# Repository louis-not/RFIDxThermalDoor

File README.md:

# RFIDxThermalDoor
[Indonesia]
Alat Pengunci Pintu Contactless berbasis RFID dan Sensor Suhu Infrared didesain dengan mempertimbangkan kondisi pandemi yang bertujuan untuk mengurangi kontak gagang pintu dengan tangan pengguna. Alat ini dapat digunakan dengan mengintegrasikan dengan sistem pengunci pintu konvensional atau sebagai mekanisme penguncian pintu atau digunakan sebagai stand-alone device.

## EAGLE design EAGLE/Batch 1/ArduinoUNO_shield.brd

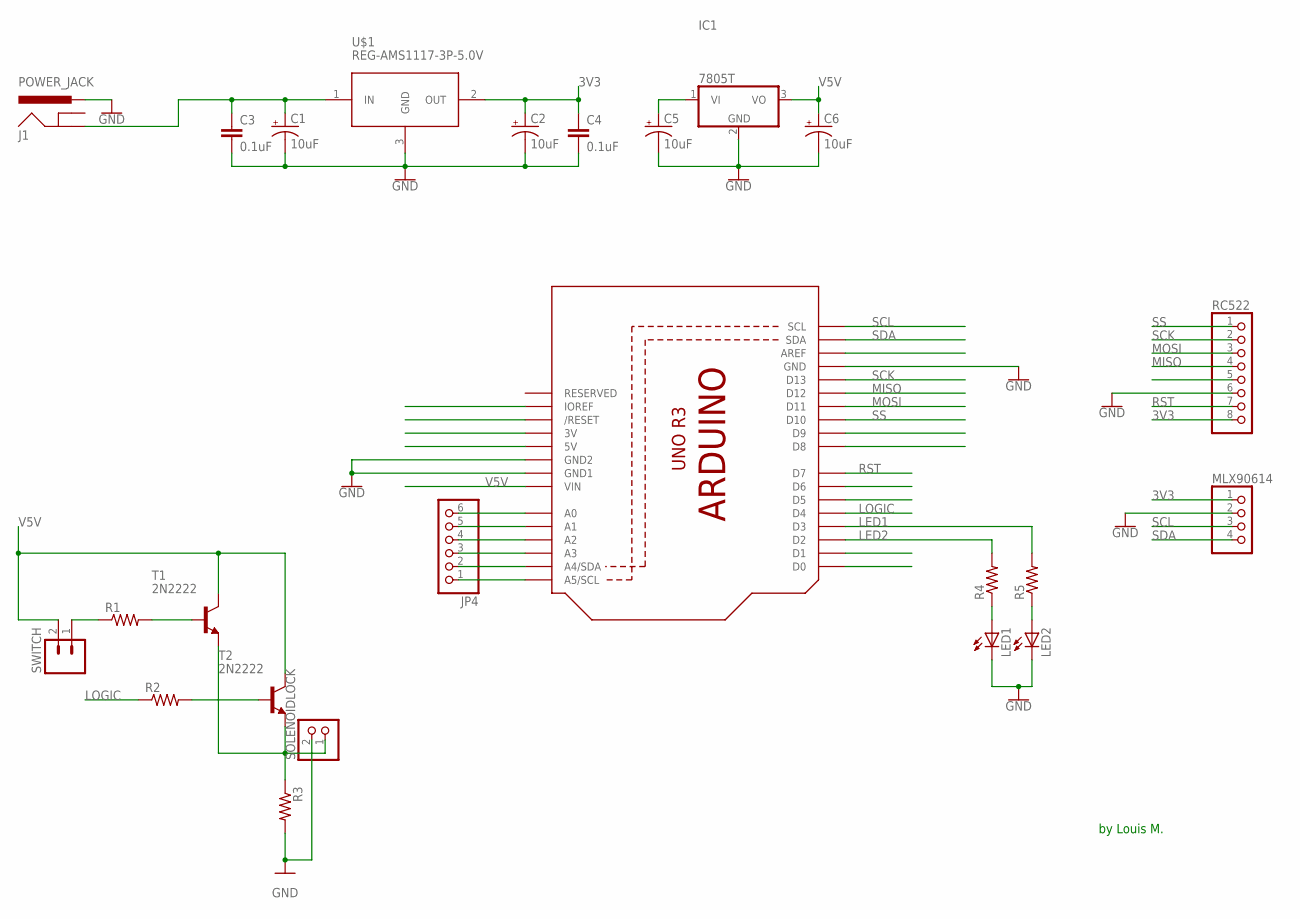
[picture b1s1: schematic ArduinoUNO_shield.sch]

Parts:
C1, C2: 10uF; CPOL-RADIAL-2.5MM-5MM-KIT
C3, C4: 0.1uF; CAP-PTH-SMALL-KIT
C5, C6: 10uF; CPOL-RADIAL-2.5MM-5MM
IC1: 7805T; TO220H
J1: POWER_JACK; POWER_JACK_PTH
JP4: PINHD-1X6B; 1X06-BIG
LED1, LED2: LED5MM
MLX90614: PINHD-1X4; 1X04
R1, R2, R3: R-US_0207/10; 0207/10
R4, R5: R-US_0204/5; 0204/5
RC522: PINHD-1X8; 1X08
SOLENOIDLOCK: JST_2PIN-THM-RA; JST-PH-2-THM-RA
SWITCH: M02; 02P
T1, T2: 2N2222; TO92-EBC-OVAL
U$1: REG-AMS1117-3P-5.0V; REG-AMS1117-3P
UNOR3: ARDUINOR3-DIMENSION; ARDUINOR3

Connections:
3V3: C2.1 (+), C4.1, MLX90614.1, RC522.8, U$1.2 (OUT)
GND: C1.2 (-), C2.2 (-), C3.2, C4.2, C5.2 (-), C6.2 (-), IC1.2 (GND), J1.PWR, LED1.K (C), LED2.K (C), MLX90614.2, R3.2, RC522.6, SOLENOIDLOCK.2 (1), U$1.3 (GND), UNOR3.GND, UNOR3.GND1, UNOR3.GND2
LED1: R5.2, UNOR3.D3
LED2: R4.2, UNOR3.D2
LOGIC: R2.1, UNOR3.D4
MISO: RC522.4, UNOR3.D12
MOSI: RC522.3, UNOR3.D11
unnamed: R1.2, T1.B
unnamed: R1.1, SWITCH.1
unnamed: R2.2, T2.B
unnamed: LED1.A, R4.1
unnamed: R3.1, SOLENOIDLOCK.1 (2), T1.E, T2.E
unnamed: LED2.A, R5.1
unnamed: C5.1 (+), IC1.1 (VI)
unnamed: C1.1 (+), C3.1, J1.GND, U$1.1 (IN)
unnamed: JP4.6, UNOR3.A0
unnamed: JP4.5, UNOR3.A1
unnamed: JP4.4, UNOR3.A2
unnamed: JP4.3, UNOR3.A3
unnamed: JP4.2, UNOR3.A4 (A4/SDA)
unnamed: JP4.1, UNOR3.A5 (A5/SCL)
RST: RC522.7, UNOR3.D7
SCK: RC522.2, UNOR3.D13
SCL: MLX90614.3, UNOR3.SCL
SDA: MLX90614.4, UNOR3.SDA
SS: RC522.1, UNOR3.D10
V5V: C6.1 (+), IC1.3 (VO), SWITCH.2, T1.C, T2.C, UNOR3.VIN

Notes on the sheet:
by Louis M.

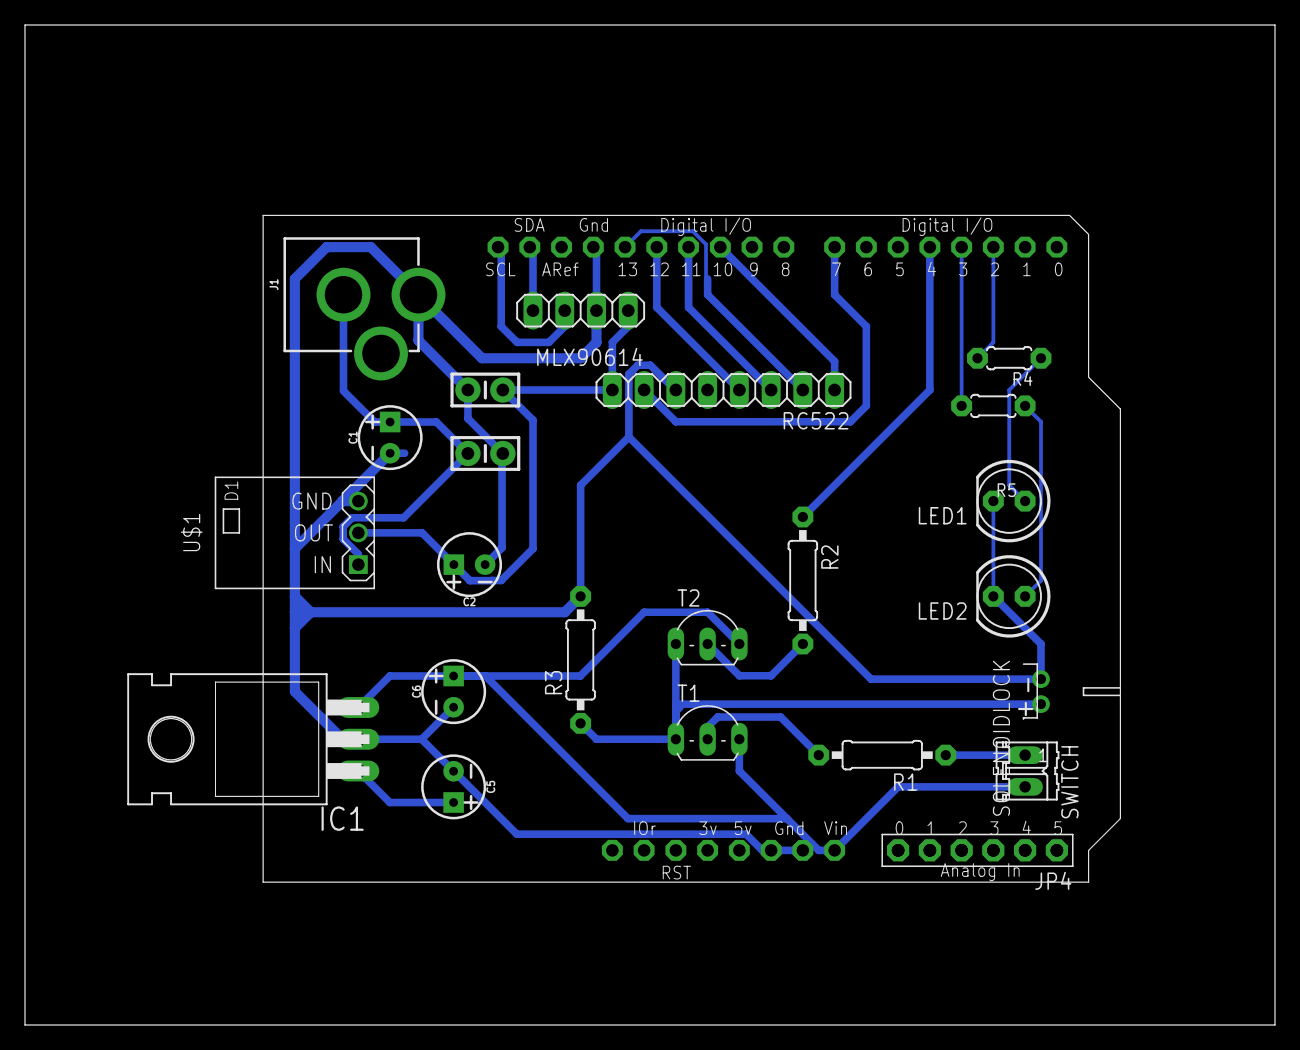
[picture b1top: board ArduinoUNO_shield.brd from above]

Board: 2 copper layers, 100.0 x 80.0 mm, 24 parts (0 on the bottom side), 27 nets.

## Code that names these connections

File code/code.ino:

#include <SPI.h>  // RFID
#include <MFRC522.h> // RFID Sensor
#include <Wire.h> // I2C, for Thermometre
#include <avr/wdt.h> // Watchdog timer
#include <Adafruit_MLX90614.h> // thermometer
#define SS_PIN 10 // RFID
#define RST_PIN 7 // RFID
#define LOGIC 4
#define LED1 2 // Red
#define LED2 3 // Blue


MFRC522 mfrc522(SS_PIN, RST_PIN); 
Adafruit_MLX90614 mlx = Adafruit_MLX90614();

void setup() {
  Serial.begin(57600) ;
  SPI.begin();
  
  // RFID Setup
  mfrc522.PCD_Init() ;
  Serial.println("Setup 1");

  // RELAY Setup
  pinMode(LOGIC, OUTPUT) ;
  Serial.println("Setup 2");
  
  // Temperature Setup
  const int constant = 1.5 ;// kalibrasi thermometer terhadap jarak pengukuran 5 cm
  mlx.begin();
  Serial.println("Setup 3");
  
  // Indicator Setup
  pinMode(LED1, OUTPUT) ;
  pinMode(LED2, OUTPUT) ;
  Serial.println("Setup 4");
  
  // Watchdog timer setup 
//  wdt_enable(WDTO_8S) ;
  Serial.println("Setup 5");
  
  // Success Setup
  for (int i = 0; i < 3 ; i++ ){
    digitalWrite(LED1, HIGH);
    delay(500) ;
    digitalWrite(LED1, LOW) ;  
  }
  Serial.println("Setup Success");
}

void loop() {
  wdt_reset() ;
//  Serial.println("Begin test") ;
  if ( ! mfrc522.PICC_IsNewCardPresent()) 
  {
    return;
  }
  // Select one of the cards
  if ( ! mfrc522.PICC_ReadCardSerial()) 
  {
    return;
  }
  Serial.println("pass") ;
  String userID = "";
  byte letter ;
  for (byte i = 0; i < mfrc522.uid.size; i++){
     Serial.print(mfrc522.uid.uidByte[i] < 0x10 ? " 0" : " ");
     Serial.print(mfrc522.uid.uidByte[i], HEX);
     userID.concat(String(mfrc522.uid.uidByte[i] < 0x10 ? " 0" : " "));
     userID.concat(String(mfrc522.uid.uidByte[i], HEX));
  }
  wdt_reset() ;
  Serial.println();
  userID.toUpperCase();
  if (userID.substring(1) == "02 AC 7E D1 E1 0E B0" || userID.substring(1) == "E5 AD 8D 4F") {
    digitalWrite(LED1, HIGH) ;
    Tempcheck() ;   
    delay(2000) ;
  } else {
    delay(2000) ;
  }

  //reset indicator
  digitalWrite(LED1, LOW);
  digitalWrite(LED2, LOW);
  Serial.println("reset complete") ;
  delay(2000);
}

void Tempcheck(){
  wdt_reset() ;
  while (1){
    float temp = mlx.readObjectTempC() ;
    if (temp > 34 && temp < 40) {
      Serial.println(temp) ;
      if (temp >= 37 ){
        digitalWrite(LED1, LOW) ;
        Serial.println("GO AWAY");
        } else {
        Serial.println("GET IN!") ;
        digitalWrite(LED2, HIGH) ;
        digitalWrite(LOGIC, HIGH) ;
        delay (5000) ;
        digitalWrite(LOGIC, LOW) ;
        }
        wdt_reset() ;
        break ;
//      Serial.println("Breaking out");
    } else {
      wdt_reset() ;
      continue ; 
    }
  }


}

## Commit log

2021-08-15 Add files via upload
    add git
2021-08-15 Add files via upload
    add drawio
2021-08-15 add PCB board

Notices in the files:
parts and their libraries:
SparkFun-Capacitors: Licensing: Creative Commons ShareAlike 4.0 International - https://creativecommons.org/licenses/by-sa/4.0
diy-modules: Released under the Creative Commons Attribution 4.0 International License: http://creativecommons.org/licenses/by/4.0
